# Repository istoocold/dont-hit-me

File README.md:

# don't hit me (handle bar)

don't hit me is a project containing multiple tools/gadgets to aid us during biking. atm there's a handle bar with indicator lights in this repo and an actual indicator for the seat in [the repo indikator](https://github.com/tanmayrajk/indikator). 

there's plans for more stuff like phone holder, some sort of communication between bikes and other stuff maybe.

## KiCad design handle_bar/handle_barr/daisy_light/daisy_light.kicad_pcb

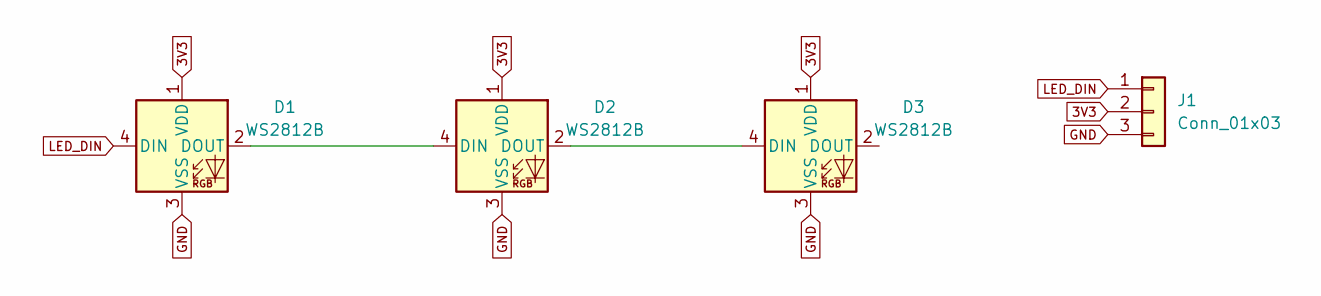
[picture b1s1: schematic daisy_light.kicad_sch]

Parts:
D1, D2, D3: WS2812B; LED_WS2812B_PLCC4_5.0x5.0mm_P3.2mm
J1: Conn_01x03; SolderWirePad_1x03_SMD_1x3mm

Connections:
3V3: D1.1 (VDD), D2.1 (VDD), D3.1 (VDD), J1.2
GND: D1.3 (VSS), D2.3 (VSS), D3.3 (VSS), J1.3
LED_DIN: D1.4 (DIN), J1.1
unnamed: D1.2 (DOUT), D2.4 (DIN)
unnamed: D2.2 (DOUT), D3.4 (DIN)

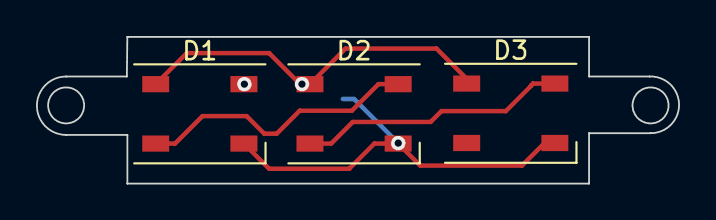
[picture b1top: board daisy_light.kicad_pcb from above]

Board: 2 copper layers, 35.7 x 8.2 mm, 4 parts (1 on the bottom side), 5 nets.

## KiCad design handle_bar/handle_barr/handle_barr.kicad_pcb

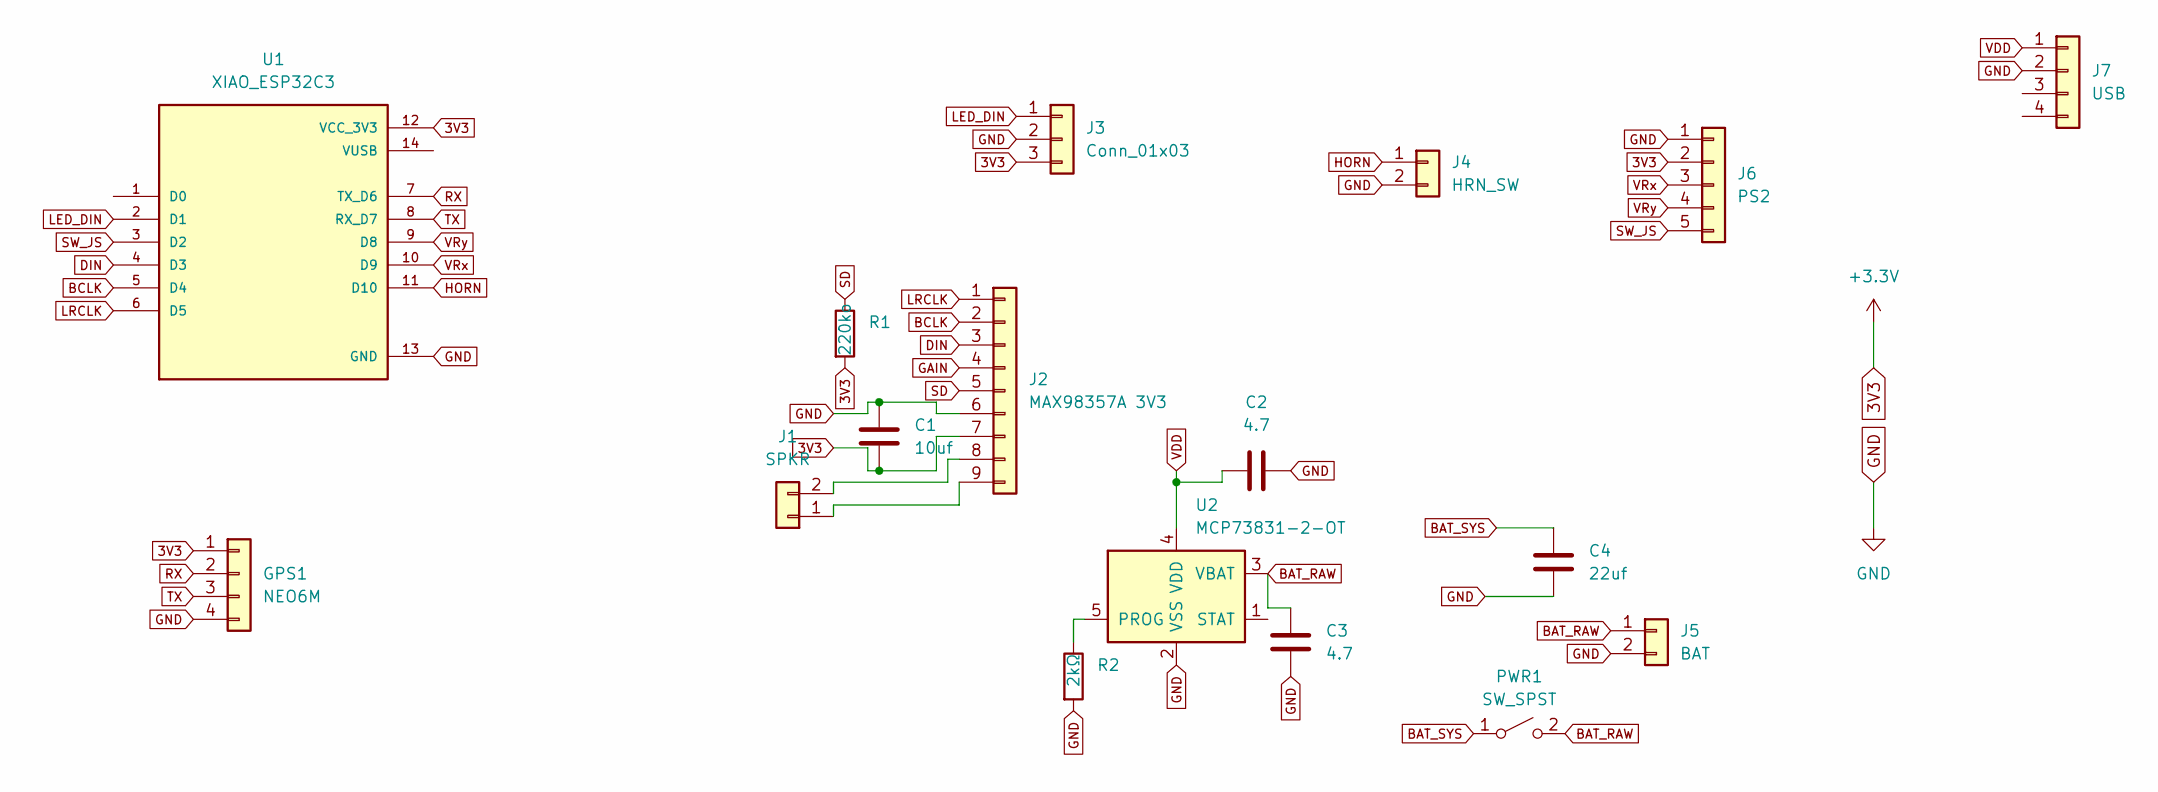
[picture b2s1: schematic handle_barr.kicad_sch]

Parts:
C1: 10uf; C_Disc_D7.5mm_W5.0mm_P5.00mm
C2, C3: 4.7; C_Disc_D6.0mm_W2.5mm_P5.00mm
C4: 22uf; CP_Radial_D5.0mm_P2.50mm
GPS1: NEO6M; SolderWirePad_1x04_SMD_1x3mm
J1: SPKR
J2: MAX98357A 3V3; SolderWirePad_1x07_SMD_1x3mm
J3: Conn_01x03; SolderWirePad_1x03_SMD_1x3mm
J4: HRN_SW; SolderWirePad_1x02_SMD_5x5mm
J5: BAT; SolderWirePad_1x02_SMD_5x5mm
J6: PS2; SolderWirePad_1x05_SMD_1x3mm
J7: USB; SolderWirePad_1x02_SMD_5x5mm
PWR1: SW_SPST; SolderWirePad_1x02_SMD_5x5mm
R1: 220ko; R_Axial_DIN0207_L6.3mm_D2.5mm_P7.62mm_Horizontal
R2: 2kΩ; R_Axial_DIN0207_L6.3mm_D2.5mm_P7.62mm_Horizontal
U1: XIAO_ESP32C3; MODULE_XIAO_ESP32C3; PARTREV 23/05/2022
U2: MCP73831-2-OT; SOT-23-5

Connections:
3V3: C1.2, GPS1.1, J2.7, J3.3, J6.2, R1.2, U1.12 (VCC_3V3)
BAT_RAW: C3.2, J5.1, PWR1.2 (B), U2.3 (VBAT)
BAT_SYS: C4.1, PWR1.1 (A); also elsewhere on the board
BCLK: J2.2, U1.5 (D4)
DIN: J2.3, U1.4 (D3)
GAIN: J2.4
GND: C1.1, C2.2, C3.1, C4.2, GPS1.4, J2.6, J3.2, J4.2, J5.2, J6.1, J7.2, R2.2, U1.13 (GND), U2.2 (VSS); also elsewhere on the board
HORN: J4.1, U1.11 (D10)
LED_DIN: J3.1, U1.2 (D1)
LRCLK: J2.1, U1.6 (D5)
unnamed: J1.1, J2.9
unnamed: J1.2, J2.8
unnamed: R2.1, U2.5 (PROG)
RX: GPS1.2, U1.7 (TX_D6)
SD: J2.5, R1.1
SW_JS: J6.5, U1.3 (D2)
TX: GPS1.3, U1.8 (RX_D7)
VDD: C2.1, J7.1, U2.4 (VDD)
VRx: J6.3, U1.10 (D9)
VRy: J6.4, U1.9 (D8)

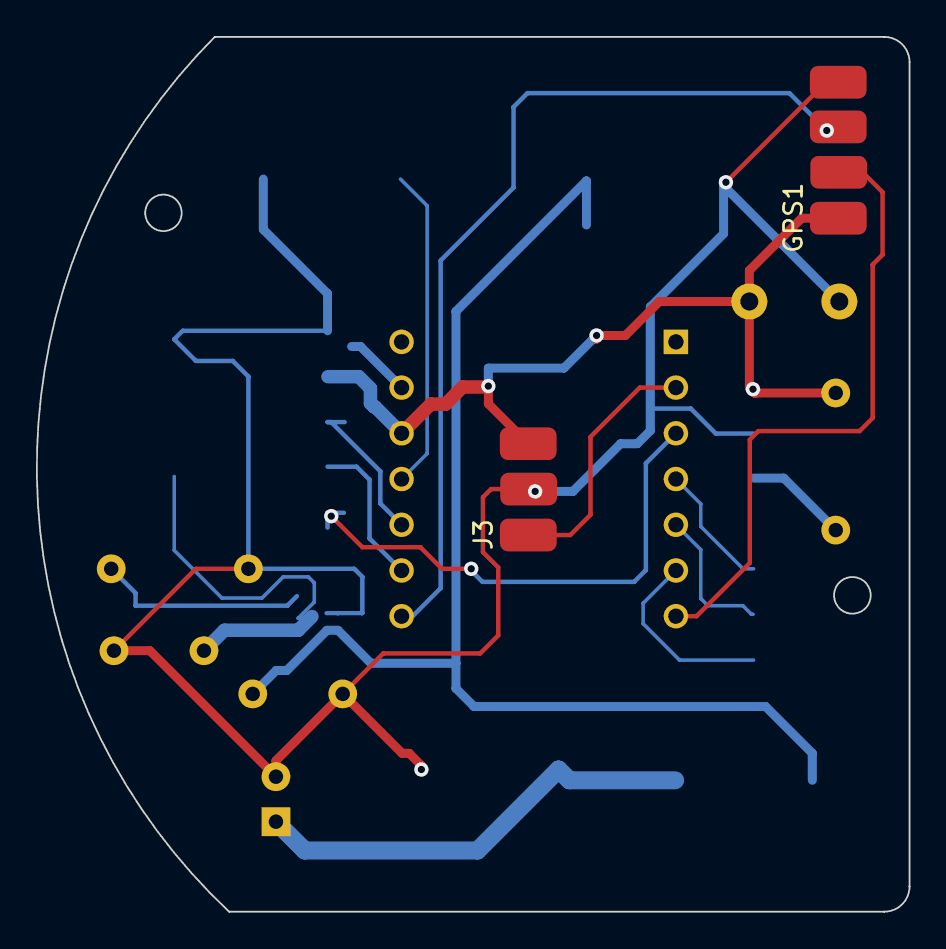
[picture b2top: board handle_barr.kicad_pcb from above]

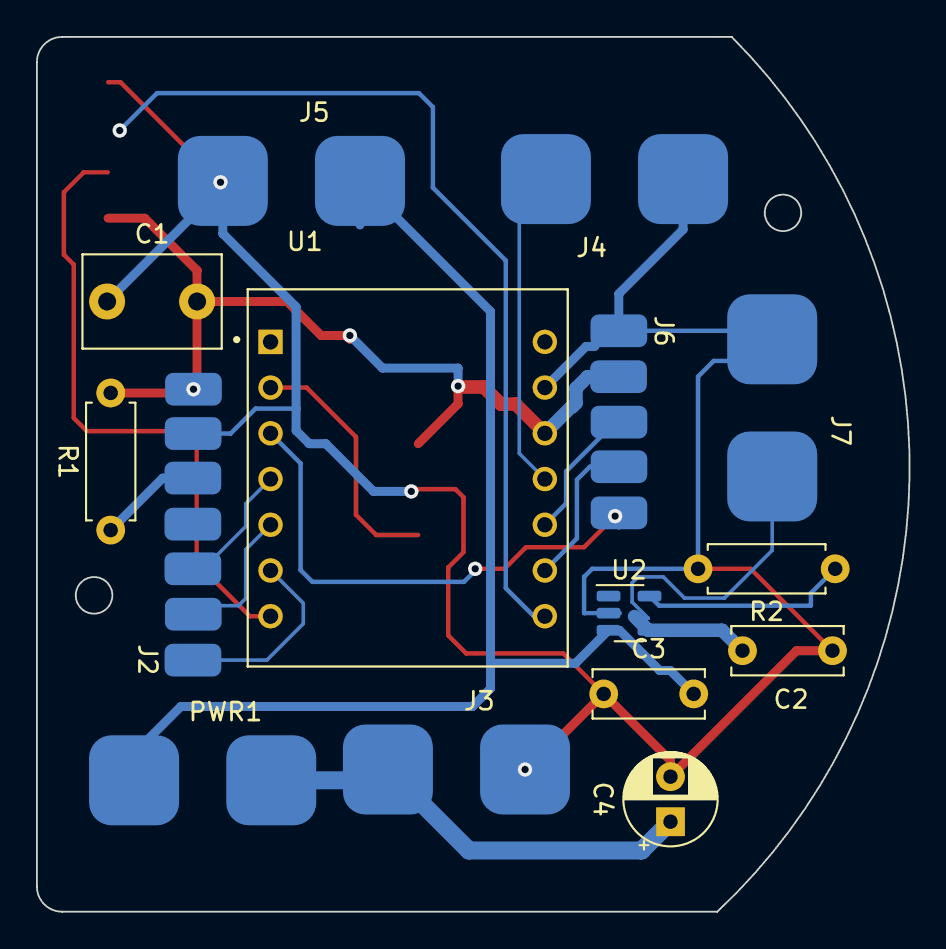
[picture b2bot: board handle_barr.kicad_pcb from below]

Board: 2 copper layers, 48.5 x 48.6 mm, 17 parts (15 on the bottom side), 17 nets.

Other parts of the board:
J3#2: PWR_SLIDE; SolderWirePad_1x02_SMD_5x5mm

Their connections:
BAT_SYS: J3#2.2; also elsewhere on the board
GND: J3#2.1; also elsewhere on the board
